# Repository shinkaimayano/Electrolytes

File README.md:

# Electrolytes

A Pro Micro based 4x10 ortholinear PCB that's compatible with the Yasui by [rainkeebs](https://github.com/rainkeebs).

Special thanks to [rlbaxter](https://github.com/rlbaxter) for the original [Electrolyte](https://github.com/rlbaxter/electrolyte) and for some ideas present in this PCB.

Some great cases that fit this PCB are the [Umō](https://github.com/pohjolaworks/Umo) by [PohjolaWorks](https://github.com/pohjolaworks) and the case by HaiZeus#0411.

The firmware can be found [here](https://github.com/shinkaimayano/Firmwares/tree/main/electrolytes/rev2.0).

## Layout and Renders

This PCB supports the all the R2 Yasui layouts as well as some more symmetrical layouts (Centered 4u, MechVault Split, etc.). OLED and RGB breakouts are provided if they are wanted as well a position for a rotary encoder in the bottom left. The KLE can be found [here](http://www.keyboard-layout-editor.com/#/gists/fb9aadbc1251c487f24355c8019214f2).

## Ordering

Current Status: **Untested** (***Order at your own risk!***)

BOM and CPL files are included in the repository, provided you want the SMD components pre-soldered by the fabricator, but if you are going to order it bare, you will need the following to make it functional:

- Required Components:
  - 31-40 MX Switches (Layout Dependent)
  - Pro-Micro (Drop-in)
  - 2 1x13 Controller Sockets
  - 40 SOD-123 Diodes
- Optional Components:
  - Reset Button

## Notes

- **The current revision (2.0) has two jumpers that need to be soldered for the matrix to be completed as this was done was as a no via challenge.**
- Cut out the _33 and 0.5u WKL layouts to fix the shorting of the original.
- A reset button was added to match the original Yasui, compared to the jumper of revision 1.0.
- The aRGB breakout was moved to near the Pro Micro in hopes that it would make soldering two rows of strips easier.
- A battery breakout was placed on the PCB so a full 1x13 pin header can be installed.
- Flex cuts were removed as they were a hindrance and was to gain PCB routing experience in that aspect.
- Slightly updated the edge cuts and tray-mount hole locations to make it a one-to-one match with the R2 Yasui Plate.
- Flipped the switch right under the Pro Micro USB to account for drop-in Pro Micros that have a USB-C that is not mid-mounted.
- Plating was added to the bottom stabilizer holes so GND can't be accidentally shorted when using screw-in stabilizers.
- The libraries used for this project are my own and [marbastlib](https://github.com/ebastler/marbastlib).
- You need at least KiCad 7 to open the source files.

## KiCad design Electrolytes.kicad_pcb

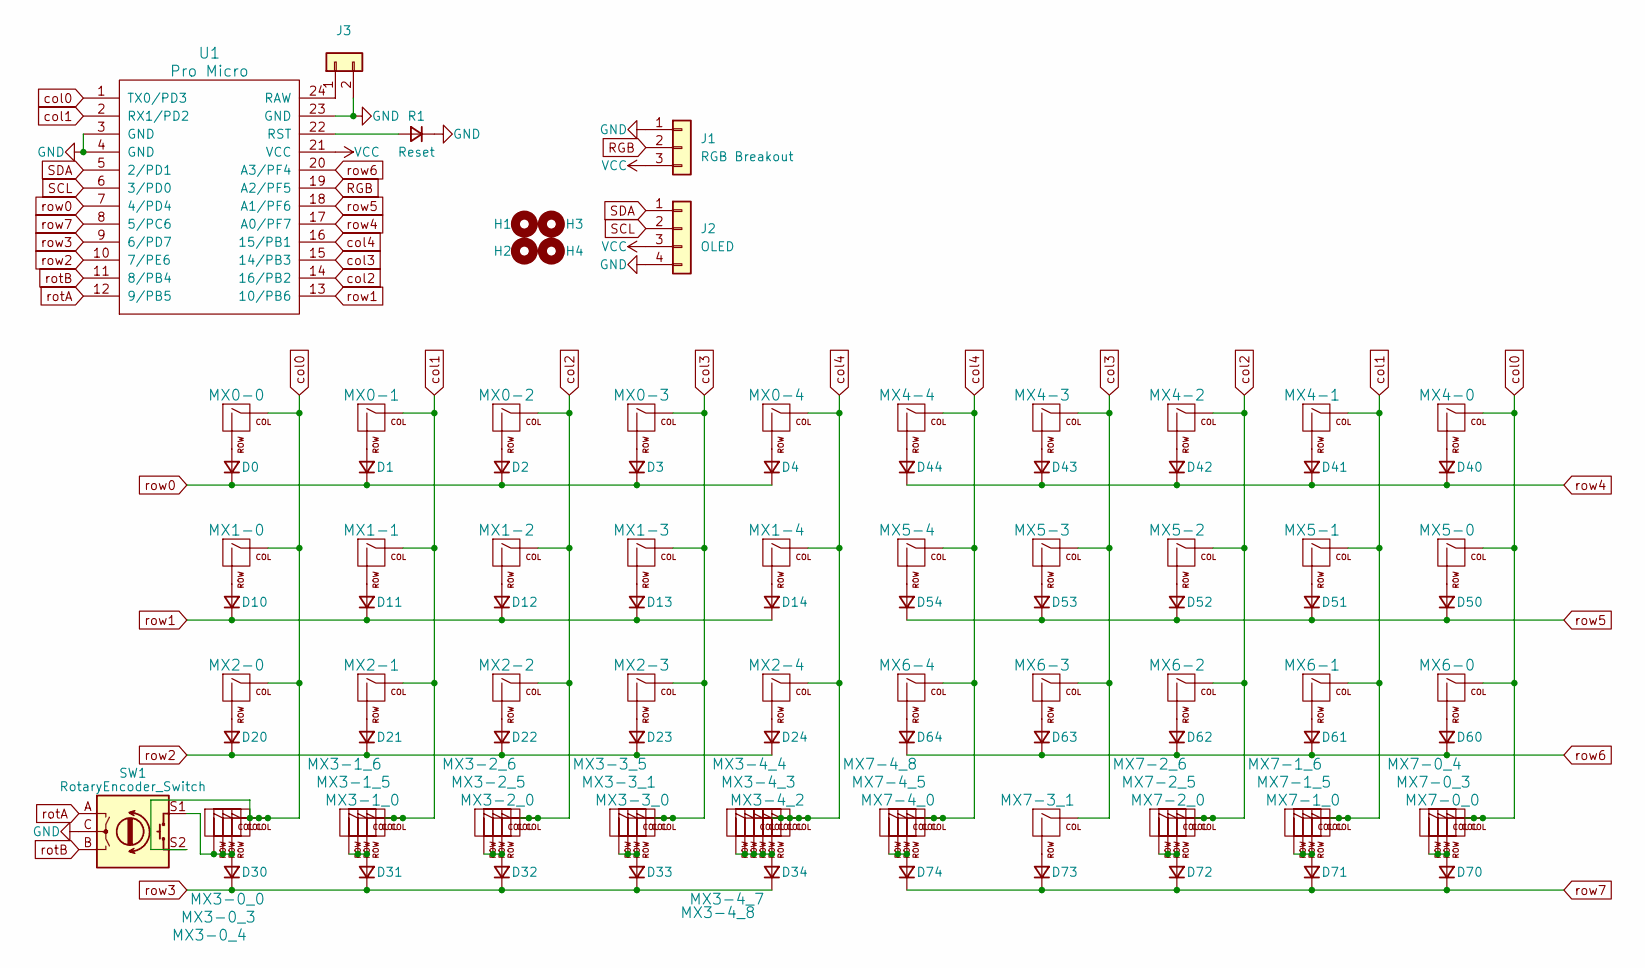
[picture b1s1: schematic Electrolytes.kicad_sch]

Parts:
D0, D1, D2, D3, D4, D10, D11, D12, D13, D14, D20, D21, D22, D23, D24, D30, D31, D32, D33, D34, D40, D41, D42, D43, D44, D50, D51, D52, D53, D54, D60, D61, D62, D63, D64, D70, D71, D72, D73, D74: D_Small; D_SOD-123
H1, H2, H3, H4: MountingHole; MountingHole_2.2mm_M2
J1: RGB Breakout; PinHeader_1x03_P2.54mm_Vertical
J2: OLED; PinHeader_1x04_P2.54mm_Vertical
J3: (no value)
MX0-0, MX0-1, MX0-2, MX0-3, MX0-4, MX1-0, MX1-1, MX1-2, MX1-3, MX1-4, MX2-0, MX2-1, MX2-2, MX2-3, MX2-4, MX3-0_0, MX3-1_0, MX3-1_6, MX3-2_0, MX3-2_5, MX3-4_8, MX4-0, MX4-1, MX4-2, MX4-3, MX4-4, MX5-0, MX5-1, MX5-2, MX5-3, MX5-4, MX6-0, MX6-1, MX6-2, MX6-3, MX6-4, MX7-0_0, MX7-1_0, MX7-1_6, MX7-2_0, MX7-2_5, MX7-4_8: MX-NoLED; MXOnly-1U-NoLED
MX3-0_3, MX7-0_3: MX-NoLED; MXOnly-1.5U-NoLED
MX3-0_4, MX3-1_5, MX3-2_6, MX7-0_4, MX7-1_5, MX7-2_6: MX-NoLED; MXOnly-1.25U-NoLED
MX3-3_0, MX3-4_7, MX7-4_0, MX7-4_5: MX-NoLED; MXOnly-2U-ReversedStabilizers-NoLED
MX3-3_1, MX7-3_1: MX-NoLED; MXOnly-3U-ReversedStabilizers-NoLED
MX3-3_5: MX-NoLED; MXOnly-2.25U-ReversedStabilizers-NoLED
MX3-4_2: MX-NoLED; MXOnly-6U-Centered-ReversedStabilizers-NoLED
MX3-4_3: MX-NoLED; MXOnly-7U-ReversedStabilizers-NoLED
MX3-4_4: MX-NoLED; MXOnly-6.25U-ReversedStabilizers-NoLED
R1: Reset; PinHeader_1x02_P2.54mm_Vertical
SW1: RotaryEncoder_Switch; RotaryEncoder_Alps_EC11E-Switch_Vertical_H20mm_No_Mounting
U1: Pro Micro; ArduinoProMicro

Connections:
GND: J1.1, J2.4, J3.2, R1.1 (K), SW1.C, U1.3 (GND), U1.4 (GND), U1.23 (GND)
unnamed: D0.2 (A), MX0-0.2 (ROW)
unnamed: D1.2 (A), MX0-1.2 (ROW)
unnamed: D2.2 (A), MX0-2.2 (ROW)
unnamed: D3.2 (A), MX0-3.2 (ROW)
unnamed: D4.2 (A), MX0-4.2 (ROW)
unnamed: D10.2 (A), MX1-0.2 (ROW)
unnamed: D11.2 (A), MX1-1.2 (ROW)
unnamed: D12.2 (A), MX1-2.2 (ROW)
unnamed: D13.2 (A), MX1-3.2 (ROW)
unnamed: D14.2 (A), MX1-4.2 (ROW)
unnamed: D20.2 (A), MX2-0.2 (ROW)
unnamed: D21.2 (A), MX2-1.2 (ROW)
unnamed: D22.2 (A), MX2-2.2 (ROW)
unnamed: D23.2 (A), MX2-3.2 (ROW)
unnamed: D24.2 (A), MX2-4.2 (ROW)
unnamed: D30.2 (A), MX3-0_0.2 (ROW), MX3-0_3.2 (ROW), MX3-0_4.2 (ROW), SW1.S1
unnamed: D31.2 (A), MX3-1_0.2 (ROW), MX3-1_5.2 (ROW), MX3-1_6.2 (ROW)
unnamed: D32.2 (A), MX3-2_0.2 (ROW), MX3-2_5.2 (ROW), MX3-2_6.2 (ROW)
unnamed: D33.2 (A), MX3-3_0.2 (ROW), MX3-3_1.2 (ROW), MX3-3_5.2 (ROW)
unnamed: D34.2 (A), MX3-4_2.2 (ROW), MX3-4_3.2 (ROW), MX3-4_4.2 (ROW), MX3-4_7.2 (ROW), MX3-4_8.2 (ROW)
unnamed: D40.2 (A), MX4-0.2 (ROW)
unnamed: D41.2 (A), MX4-1.2 (ROW)
unnamed: D42.2 (A), MX4-2.2 (ROW)
unnamed: D43.2 (A), MX4-3.2 (ROW)
unnamed: D44.2 (A), MX4-4.2 (ROW)
unnamed: D50.2 (A), MX5-0.2 (ROW)
unnamed: D51.2 (A), MX5-1.2 (ROW)
unnamed: D52.2 (A), MX5-2.2 (ROW)
unnamed: D53.2 (A), MX5-3.2 (ROW)
unnamed: D54.2 (A), MX5-4.2 (ROW)
unnamed: D60.2 (A), MX6-0.2 (ROW)
unnamed: D61.2 (A), MX6-1.2 (ROW)
unnamed: D62.2 (A), MX6-2.2 (ROW)
unnamed: D63.2 (A), MX6-3.2 (ROW)
unnamed: D64.2 (A), MX6-4.2 (ROW)
unnamed: D70.2 (A), MX7-0_0.2 (ROW), MX7-0_3.2 (ROW), MX7-0_4.2 (ROW)
unnamed: D71.2 (A), MX7-1_0.2 (ROW), MX7-1_5.2 (ROW), MX7-1_6.2 (ROW)
unnamed: D72.2 (A), MX7-2_0.2 (ROW), MX7-2_5.2 (ROW), MX7-2_6.2 (ROW)
unnamed: D73.2 (A), MX7-3_1.2 (ROW)
unnamed: D74.2 (A), MX7-4_0.2 (ROW), MX7-4_5.2 (ROW), MX7-4_8.2 (ROW)
unnamed: J3.1, U1.24 (RAW)
unnamed: R1.2 (A), U1.22 (RST)
RGB: J1.2, U1.19 (A2/PF5)
SCL: J2.2, U1.6 (3/PD0)
SDA: J2.1, U1.5 (2/PD1)
VCC: J1.3, J2.3, U1.21 (VCC)
col0: MX0-0.1 (COL), MX1-0.1 (COL), MX2-0.1 (COL), MX3-0_0.1 (COL), MX3-0_3.1 (COL), MX3-0_4.1 (COL), MX4-0.1 (COL), MX5-0.1 (COL), MX6-0.1 (COL), MX7-0_0.1 (COL), MX7-0_3.1 (COL), MX7-0_4.1 (COL), SW1.S2, U1.1 (TX0/PD3)
col1: MX0-1.1 (COL), MX1-1.1 (COL), MX2-1.1 (COL), MX3-1_0.1 (COL), MX3-1_5.1 (COL), MX3-1_6.1 (COL), MX4-1.1 (COL), MX5-1.1 (COL), MX6-1.1 (COL), MX7-1_0.1 (COL), MX7-1_5.1 (COL), MX7-1_6.1 (COL), U1.2 (RX1/PD2)
col2: MX0-2.1 (COL), MX1-2.1 (COL), MX2-2.1 (COL), MX3-2_0.1 (COL), MX3-2_5.1 (COL), MX3-2_6.1 (COL), MX4-2.1 (COL), MX5-2.1 (COL), MX6-2.1 (COL), MX7-2_0.1 (COL), MX7-2_5.1 (COL), MX7-2_6.1 (COL), U1.14 (16/PB2)
col3: MX0-3.1 (COL), MX1-3.1 (COL), MX2-3.1 (COL), MX3-3_0.1 (COL), MX3-3_1.1 (COL), MX3-3_5.1 (COL), MX4-3.1 (COL), MX5-3.1 (COL), MX6-3.1 (COL), MX7-3_1.1 (COL), U1.15 (14/PB3)
col4: MX0-4.1 (COL), MX1-4.1 (COL), MX2-4.1 (COL), MX3-4_2.1 (COL), MX3-4_3.1 (COL), MX3-4_4.1 (COL), MX3-4_7.1 (COL), MX3-4_8.1 (COL), MX4-4.1 (COL), MX5-4.1 (COL), MX6-4.1 (COL), MX7-4_0.1 (COL), MX7-4_5.1 (COL), MX7-4_8.1 (COL), U1.16 (15/PB1)
rotA: SW1.A, U1.12 (9/PB5)
rotB: SW1.B, U1.11 (8/PB4)
row0: D0.1 (K), D1.1 (K), D2.1 (K), D3.1 (K), D4.1 (K), U1.7 (4/PD4)
row1: D10.1 (K), D11.1 (K), D12.1 (K), D13.1 (K), D14.1 (K), U1.13 (10/PB6)
row2: D20.1 (K), D21.1 (K), D22.1 (K), D23.1 (K), D24.1 (K), U1.10 (7/PE6)
row3: D30.1 (K), D31.1 (K), D32.1 (K), D33.1 (K), D34.1 (K), U1.9 (6/PD7)
row4: D40.1 (K), D41.1 (K), D42.1 (K), D43.1 (K), D44.1 (K), U1.17 (A0/PF7)
row5: D50.1 (K), D51.1 (K), D52.1 (K), D53.1 (K), D54.1 (K), U1.18 (A1/PF6)
row6: D60.1 (K), D61.1 (K), D62.1 (K), D63.1 (K), D64.1 (K), U1.20 (A3/PF4)
row7: D70.1 (K), D71.1 (K), D72.1 (K), D73.1 (K), D74.1 (K), U1.8 (5/PC6)

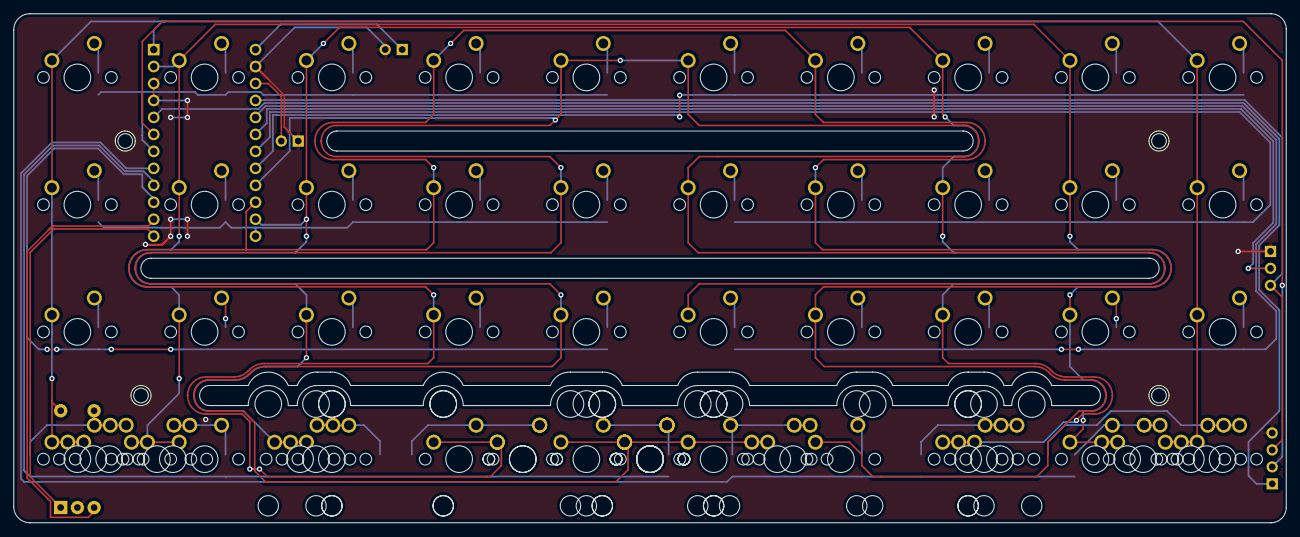
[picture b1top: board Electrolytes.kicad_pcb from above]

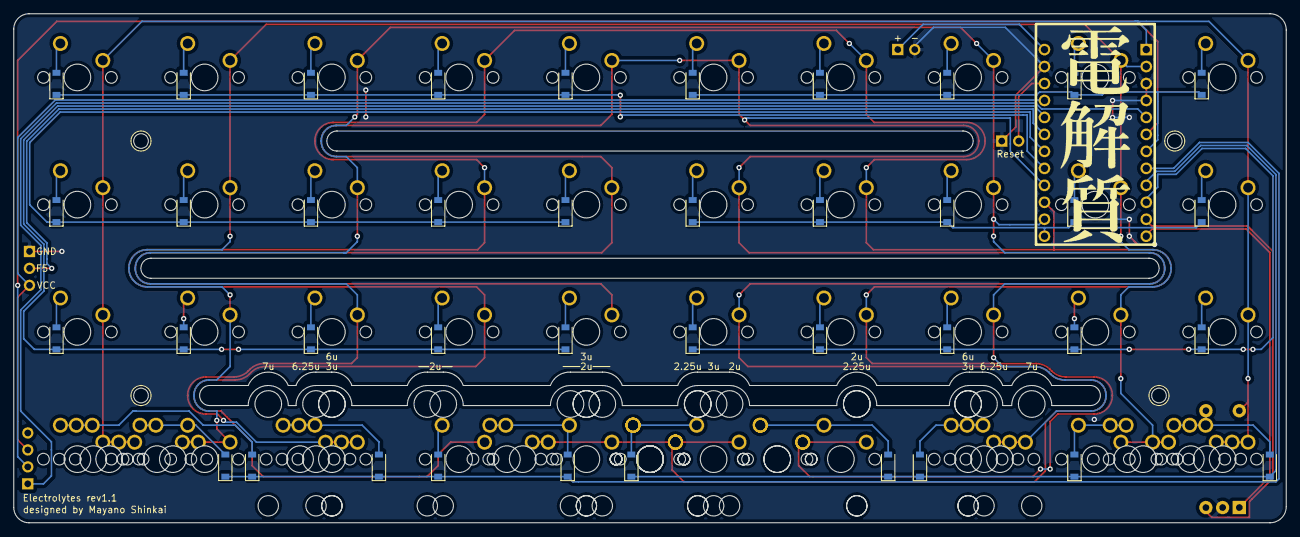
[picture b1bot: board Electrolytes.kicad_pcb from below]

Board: 2 copper layers, 190.5 x 76.2 mm, 111 parts (42 on the bottom side), 62 nets.

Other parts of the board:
Ge: LOGO

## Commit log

2022-03-28 rev 1.1
    Changed battery breakout to pin header footprint, fixed OLED orientation, adjusted top-left tray mount hole to match yasui plate
2023-08-03 rev 2.0 release
2023-08-03 rev 2.0 release
    removed extra rev1.1 production files
2023-08-03 fixed images?
2023-08-03 drc/erc clean up
